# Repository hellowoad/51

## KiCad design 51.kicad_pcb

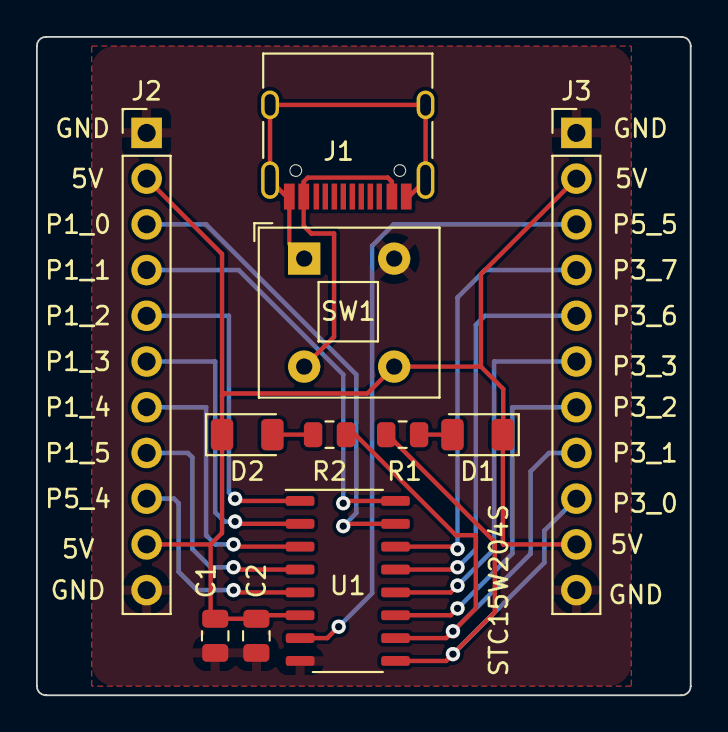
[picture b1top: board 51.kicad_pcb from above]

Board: 2 copper layers, 36.3 x 36.6 mm, 11 parts (0 on the bottom side), 20 nets.

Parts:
C1: 47uF; C_0805_2012Metric
C2: 0.1uF; C_0805_2012Metric
D1, D2: LED; LED_1206_3216Metric
J1: USB_C_Receptacle_USB2.0; USB_C_Receptacle_HRO_TYPE-C-31-M-12
J2, J3: Conn_01x11; PinHeader_1x11_P2.54mm_Vertical
R1, R2: 10k; R_0805_2012Metric
SW1: SW_DPST; SW_Push_2P1T_Toggle_CK_PVA1xxH4xxxxxxV2
U1: STC15W204S-35x-SOP16; STC_SOP-16_3.9x9.9mm_P1.27mm

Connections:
+5V: J1.A4 (VBUS), J1.A9 (VBUS), J1.B4 (VBUS), J1.B9 (VBUS), SW1.3
GND: J1.A1 (GND), J1.A12 (GND), J1.B1 (GND), J1.B12 (GND), J1.S1 (SHIELD), SW1.1
GND1: C1.2, C2.2, J2.1, J2.11, J3.1, J3.11, SW1.2, U1.8 (GND)
unnamed: D1.2 (A), R1.2
unnamed: D2.2 (A), R2.1
VCC: C1.1, C2.1, D1.1 (K), D2.1 (K), J2.2, J2.10, J3.2, J3.10, SW1.4, U1.6 (VCC)
p1_0: J2.3, U1.15 (P1.0/RSTOUT_LOW)
p1_1: J2.4, U1.16 (P1.1)
p1_2: J2.5, U1.1 (P1.2/CMPO/T0)
p1_3: J2.6, U1.2 (P1.3)
p1_4: J2.7, U1.3 (P1.4/T0CLKO)
p1_5: J2.8, U1.4 (P1.5)
p3_0: J3.9, R1.1, U1.9 (RxD/~INT4/T2CLKO/P3.0)
p3_1: J3.8, R2.2, U1.10 (TxD/T2/P3.1)
p3_2: J3.7, U1.11 (INT0/P3.2)
p3_3: J3.6, U1.12 (INT1/P3.3)
p3_6: J3.5, U1.13 (~INT2/RxD_2/P3.6)
p3_7: J3.4, U1.14 (~INT3/TxD_2/P3.7)
p5_4: J2.9, U1.5 (CMP-/MCLKO/RST/P5.4)
p5_5: J3.3, U1.7 (CMP+/P5.5)

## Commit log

2022-09-26 add switch */ /
2022-09-27 add cooper
2022-09-28 relayout
